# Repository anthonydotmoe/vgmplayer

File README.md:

# RP2040 → YM2151 VGM Player

"It's a work in progress"

### Backstory

**2018**
This project started out using an ATMEGA328P and Arduino, but I found that it
was hard to write fast enough code to play songs at full speed. I then found
the STM32 series of microcontrollers; It was promising, but I really didn't like
the SDK or the HAL that was provided for these parts. After a few years, the
Raspberry Pi Foundation released the Raspberry Pi Pico. I bought the board
during its pre-order stage simply because it's a $5 microcontroller. This new
board, with their own RP2040 chip, has one key feature that I didn't know at the
time will make this project viable for me. The Programmable I/O (PIO).

**2022**
I finally got to looking at the datasheet for this board during DEFCON 2022,
where they used the RP2040 for their interactive badge. The PIO section caught
my eye, but I didn't look into it until a month later.

When I read the examples they had for driving WS2812 LED strips, I realized
what I could do with this extra power. I could easily get data to the chip on
time, every time; and have plenty of time for drawing a UI to a screen,
fetching data from an SD card over SPI, and in the future, emulating other
sound chips for game systems with AD/PCM and other chips.

### Hardware

I made this development board for the project.

GPIO 0-7 are connected to D0-D7 on the YM2151. GPIO 8-10 are connected to the
`A0`, `WR`, and `CS` pins. I'm using SPI to connect to the SD card, and an
LTC6903 programmable clock generator making the main clock for the YM2151.

The supporting circuitry for the YM2151 was ripped from the same place I got
the chip from, a Yamaha CX5 Music Computer.

### Software

*To be documented... and written*

### Thank You

Special thanks to:

- [ReimuNotMoe](https://github.com/ReimuNotMoe) for their work on
  [TinyVGM](https://github.com/SudoMaker/TinyVGM). This framework for digesting
  the `.vgm` files is really helpful for me.
- [Aidan Lawrence](https://github.com/AidanHockey5) for open-sourcing his
  [YM2151 music player](https://github.com/AidanHockey5/YM2151_VGM_STM32) which
  got me started in the ATMEGA328P days.

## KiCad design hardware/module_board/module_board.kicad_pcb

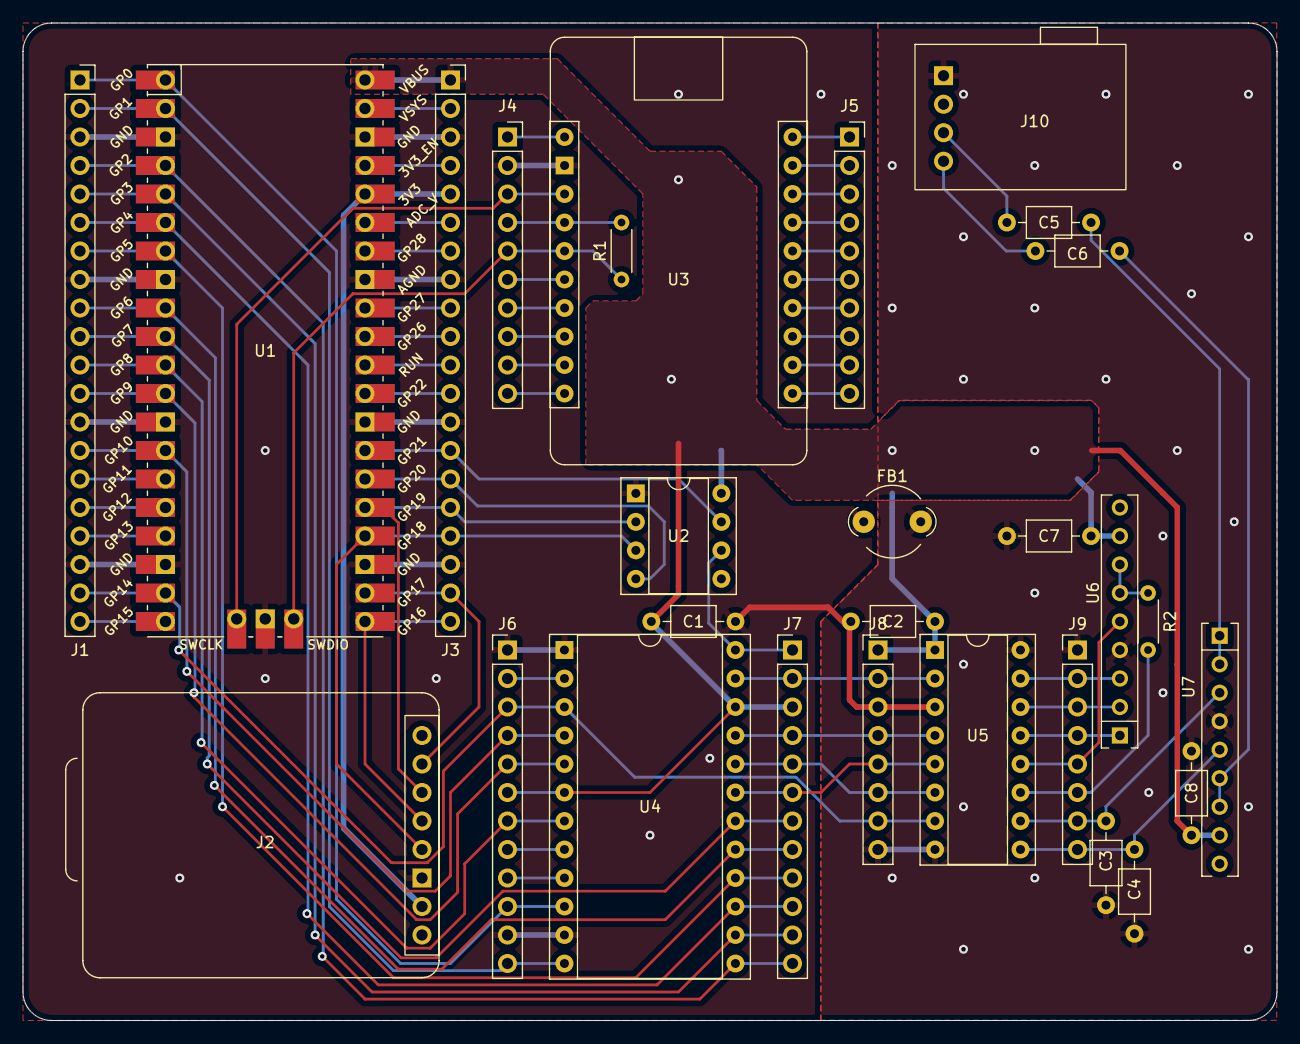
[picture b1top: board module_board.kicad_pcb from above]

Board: 2 copper layers, 111.8 x 88.9 mm, 28 parts (0 on the bottom side), 73 nets.

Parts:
C1, C2, C7, C8: 100nF; C_Axial_L3.8mm_D2.6mm_P7.50mm_Horizontal
C3, C4: 3300pF; C_Axial_L3.8mm_D2.6mm_P7.50mm_Horizontal
C5, C6: C; C_Axial_L3.8mm_D2.6mm_P7.50mm_Horizontal
FB1: 220Ω at 100MHz; LairdTech_28C0236-0JW-10
J1, J3: Conn_01x20_Female; PinSocket_1x20_P2.54mm_Vertical
J2: Micro_SD_Card_Breakout; Adafruit_Micro-SD_Card_Breakout
J4, J5: Conn_01x10_Female; PinSocket_1x10_P2.54mm_Vertical
J6, J7: Conn_01x12_Female; PinHeader_1x12_P2.54mm_Vertical
J8, J9: Conn_01x08_Female; PinHeader_1x08_P2.54mm_Vertical
J10: AudioJack4
R1: 1k; R_Axial_DIN0204_L3.6mm_D1.6mm_P5.08mm_Horizontal
R2: 100; R_Axial_DIN0204_L3.6mm_D1.6mm_P5.08mm_Horizontal
U1: Pico; RPi_Pico_SMD_TH
U2: LTC6903; DIP-8_W7.62mm_Socket
U3: FT232H_Breakout; Adafruit_FT232H_Breakout
U4: YM2151; DIP-24_W15.24mm_Socket
U5: YM3012; DIP-16_W7.62mm_Socket
U6, U7: NJM4556A; SIP-9_22.3x3mm_P2.54mm

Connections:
2151CLK: J7.1, U2.6 (CLK), U4.24 (ϕM)
+3V3: J2.7 (3V), J3.5, U1.36 (3V3)
/LTC OE: J3.14, U1.27 (GPIO21), U2.7 (OE)
/LTC ~CS: J3.15, U1.26 (GPIO20), U2.4 (~CS)
/SD ~CS: J2.2 (~CS), J3.19, U1.22 (GPIO17)
/SPI0 MISO: J2.4 (DO), J3.20, U1.21 (GPIO16)
/SPI0 MOSI: J2.3 (DI), J3.16, U1.25 (GPIO19), U2.2 (SDI)
/SPI0 SCK: J2.5 (CLK), J3.17, U1.24 (GPIO18), U2.3 (SCK)
/SWCLK: J4.3, U1.41 (SWCLK), U3.3 (D0)
/SWDIO: J4.5, R1.1, U1.43 (SWDIO), U3.5 (D2)
/YM_Output/3012CLK: J7.2, J8.2, U4.23 (ϕ1), U5.2 (CLKϕ1)
/YM_Output/BC: J9.3, U5.14 (BC), U6.2 (-)
/YM_Output/CH-1: C4.1, J9.8, U5.9 (OUT-CH1), U7.5 (+)
/YM_Output/CH-2: C3.1, J9.7, U5.10 (OUT-CH2), U7.3 (+)
/YM_Output/COM: J9.6, R2.1, U5.11 (COM)
/YM_Output/CT1: J6.8, U4.8 (CT1)
/YM_Output/CT2: J6.9, U4.9 (CT2)
/YM_Output/L-OUT_{AMP}: C6.1, U7.6 (-), U7.7
/YM_Output/MP: J9.4, U5.13 (MP), U6.1
/YM_Output/OUT-L: C6.2, J10.4 (T)
/YM_Output/OUT-R: C5.2, J10.3 (R1)
/YM_Output/R-OUT_{AMP}: C5.1, U7.1, U7.2 (-)
/YM_Output/R_{B}: J9.2, U5.15 (RB), U6.3 (+)
/YM_Output/SH1: J7.5, J8.6, U4.20 (SHI1), U5.6 (SAM1)
/YM_Output/SH2: J7.6, J8.5, U4.19 (SHI2), U5.5 (SAM2)
/YM_Output/SO: J7.4, J8.4, U4.21 (SO), U5.4 (DATA)
/YM_Output/ToBUFF: J9.5, U5.12 (ToBUFF), U6.5 (+)
/YM_Output/~IRQ: J6.2, U4.2 (~IRQ)
D0: J1.1, J6.10, U1.1 (GPIO0), U4.10 (D0)
D1: J1.2, J6.12, U1.2 (GPIO1), U4.12 (D1)
D2: J1.4, J7.12, U1.4 (GPIO2), U4.13 (D2)
D3: J1.5, J7.11, U1.5 (GPIO3), U4.14 (D3)
D4: J1.6, J7.10, U1.6 (GPIO4), U4.15 (D4)
D5: J1.7, J7.9, U1.7 (GPIO5), U4.16 (D5)
D6: J1.9, J7.8, U1.9 (GPIO6), U4.17 (D6)
D7: J1.10, J7.7, U1.10 (GPIO7), U4.18 (D7)
GNDA: C3.2, C4.2, C7.2, C8.2, FB1.2, J8.8, J9.1, J10.1 (S), U5.8 (AGND(VSS)), U5.16 (AGND(VSS)), U6.4 (V-), U7.4 (V-)
GNDD: C1.1, C2.2, FB1.1, J1.3, J1.8, J1.13, J1.18, J2.6 (GND), J3.3, J3.8, J3.13, J3.18, J4.2, J6.1, J6.11, J8.3, U1.3 (GND), U1.8 (GND), U1.13 (GND), U1.18 (GND), U1.23 (GND), U1.28 (GND), U1.33 (AGND), U1.38 (GND), U1.42 (GND), U2.1 (GND), U3.2 (GND), U4.1 (Vss(GND)), U4.11 (Vss(GND)), U5.3 (DGND(VSS))
unnamed: J1.15, U1.15 (GPIO11)
unnamed: J1.16, U1.16 (GPIO12)
unnamed: J1.17, U1.17 (GPIO13)
unnamed: J1.20, U1.20 (GPIO15)
unnamed: J3.2, U1.39 (VSYS)
unnamed: J3.4, U1.37 (3V3_EN)
unnamed: J3.6, U1.35 (ADC_VREF)
unnamed: J3.7, U1.34 (GPIO28_ADC2)
unnamed: J3.9, U1.32 (GPIO27_ADC1)
unnamed: J3.10, U1.31 (GPIO26_ADC0)
unnamed: J3.11, U1.30 (RUN)
unnamed: J3.12, U1.29 (GPIO22)
unnamed: J4.1, U3.1 (5V)
unnamed: J4.4, R1.2, U3.4 (D1)
unnamed: J4.6, U3.6 (D3)
unnamed: J4.7, U3.7 (D4)
unnamed: J4.8, U3.8 (D5)
unnamed: J4.9, U3.9 (D6)
unnamed: J4.10, U3.10 (D7)
unnamed: J5.1, U3.20 (C9)
unnamed: J5.2, U3.19 (C8)
unnamed: J5.3, U3.18 (C7)
unnamed: J5.4, U3.17 (C6)
unnamed: J5.5, U3.16 (C5)
unnamed: J5.6, U3.15 (C4)
unnamed: J5.7, U3.14 (C3)
unnamed: J5.8, U3.13 (C2)
unnamed: J5.9, U3.12 (C1)
unnamed: J5.10, U3.11 (C0)
unnamed: R2.2, U6.6 (-), U6.7
YM A0: J1.14, J6.4, U1.14 (GPIO10), U4.4 (A0)
YM ~CS: J1.11, J6.7, U1.11 (GPIO8), U4.7 (~CS)
YM ~RD: C1.2, C2.1, C7.1, C8.1, J3.1, J6.6, J7.3, J8.1, U1.40 (VBUS), U2.8 (V+), U4.6 (~RD), U4.22 (VDD(+5V)), U5.1 (VDD), U6.8 (V+), U7.8 (V+)
YM ~WR: J1.12, J6.5, U1.12 (GPIO9), U4.5 (~WR)
~ICL: J1.19, J6.3, J8.7, U1.19 (GPIO14), U4.3 (~IC), U5.7 (~ICL)

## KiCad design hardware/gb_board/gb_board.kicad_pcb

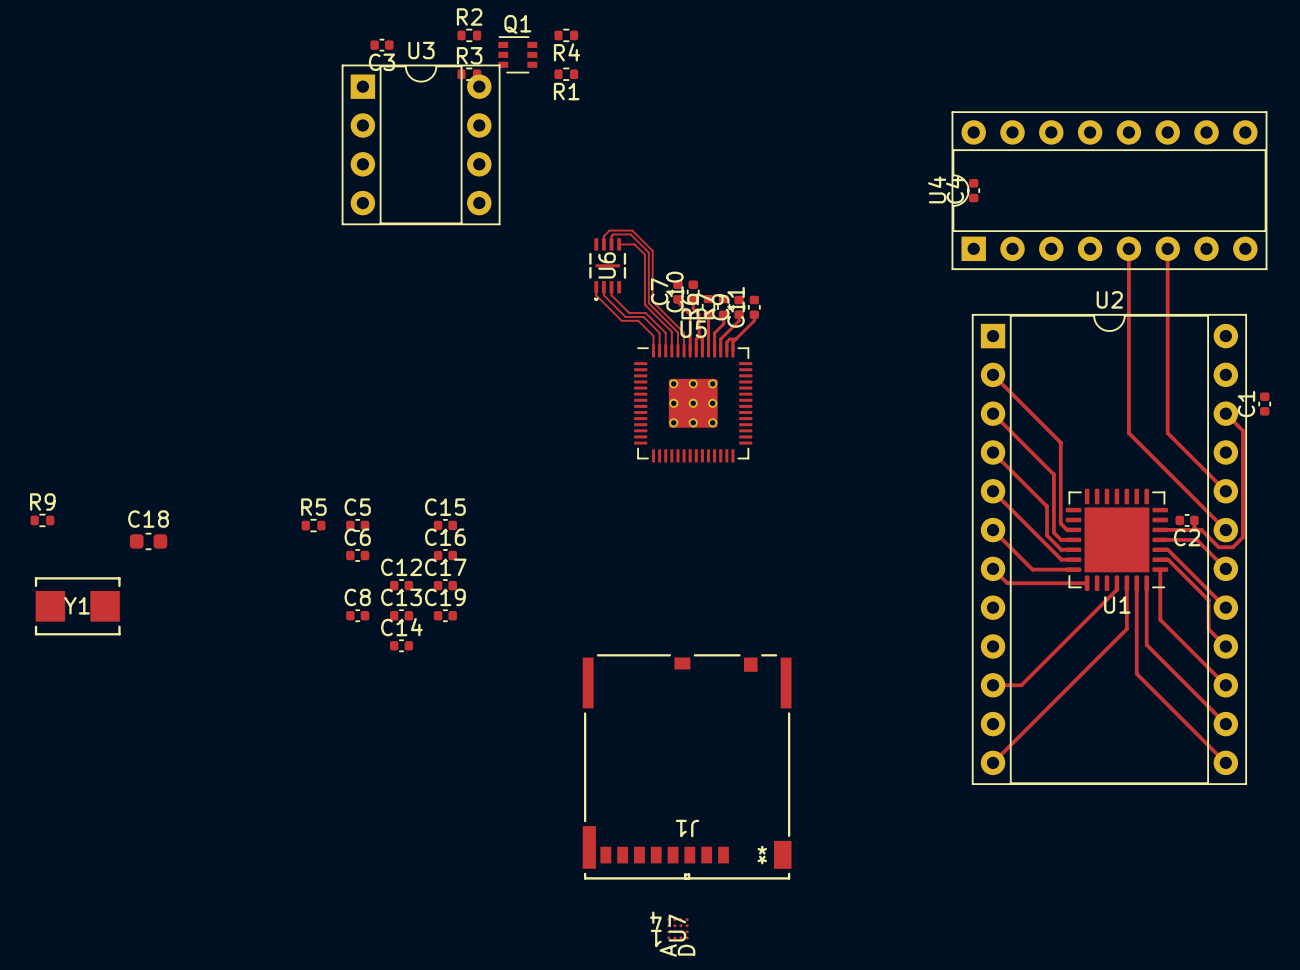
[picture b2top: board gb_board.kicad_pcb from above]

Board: 2 copper layers, 37 parts (0 on the bottom side), 40 nets.

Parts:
C1, C2, C3, C4: 0.1uF; C_0402_1005Metric
C5, C6: 27p; C_0402_1005Metric
C7, C8, C9, C10, C11, C12, C13, C14, C15, C16, C17, C19: 100n; C_0402_1005Metric
C18: 10u; C_0603_1608Metric
J1: Micro_SD_Card_Det1; 503398-1892_MOL
Q1: BSS138PS; SOT-363_SC-70-6
R1, R2, R3, R4: 10k; R_0402_1005Metric
R5: 1k; R_0402_1005Metric
R6, R7: 27.4; R_0402_1005Metric
R9: DNF; R_0402_1005Metric
U1: MCP23017_ML; QFN-28-1EP_6x6mm_P0.65mm_EP4.25x4.25mm
U2: YM2151; DIP-24_W15.24mm_Socket
U3: LTC6903; DIP-8_W7.62mm_Socket
U4: YM3012; DIP-16_W7.62mm_Socket
U5: RP2040; RP2040-QFN-56
U6: W25Q16JVUXIQ; W25Q16JVUXIQ_WIN
U7: EMIF06-MSD04F3; FLIPCHIP16_STM
Y1: ABM3-12.000MHZ-D2Y-T; XTAL_ABM3_ABR

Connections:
+1V1: C7.1, C8.1, C9.1, U5.23 (DVDD), U5.45 (VREG_VOUT), U5.50 (DVDD)
+3V3: C3.1, C10.1, C11.1, C12.1, C13.1, C14.1, C15.1, C16.1, C17.1, C18.1, C19.1, J1.4 (VDD), Q1.2 (G1), Q1.5 (G2), R1.1, R2.1, R9.1, U3.8 (V+), U5.1 (IOVDD), U5.10 (IOVDD), U5.22 (IOVDD), U5.33 (IOVDD), U5.42 (IOVDD), U5.43 (ADC_AVDD), U5.44 (VREG_IN), U5.48 (USB_VDD), U5.49 (IOVDD), U6.8 (VCC)
+5V: C1.1, C2.1, C4.1, R3.1, R4.1, U1.5 (VDD), U2.22 (VDD(+5V)), U4.1 (VDD)
/RP2040/QSPI_D0: U5.53 (QSPI_SD0), U6.5 (DI(IO0))
/RP2040/QSPI_D1: U5.55 (QSPI_SD1), U6.2 (DO(IO1))
/RP2040/QSPI_D2: U5.54 (QSPI_SD2), U6.3 (IO2)
/RP2040/QSPI_D3: U5.51 (QSPI_SD3), U6.7 (IO3)
/RP2040/QSPI_F_~CS: R9.2, U5.56 (QSPI_SS), U6.1 (~CS)
/RP2040/QSPI_SCK: U5.52 (QSPI_SCLK), U6.6 (CLK)
/RP2040/RPUSB_N: R7.1, U5.46 (USB_DM)
/RP2040/RPUSB_P: R6.1, U5.47 (USB_DP)
/RP2040/SD_DET: J1.10 (DET_A), U5.36 (GPIO24)
/SAM1: U2.20 (SHI1), U4.6 (SAM1)
/SAM2: U2.19 (SHI2), U4.5 (SAM2)
/YM_SD: U2.21 (SO), U4.4 (DATA)
GNDA: C4.2, U4.8 (AGND(VSS)), U4.16 (AGND(VSS))
GNDD: C1.2, C2.2, C3.2, C5.1, C6.1, C7.2, C8.2, C9.2, C10.2, C11.2, C12.2, C13.2, C14.2, C15.2, C16.2, C17.2, C18.2, C19.2, J1.6 (VSS), J1.9 (DET_B), J1.11 (SHIELD), U1.6 (VSS), U1.11 (A0), U1.12 (A1), U1.13 (A2), U1.29 (EP), U2.1 (Vss(GND)), U2.11 (Vss(GND)), U3.1 (GND), U4.3 (DGND(VSS)), U6.4 (GND)
unnamed: C6.2, R5.1, Y1.2
unnamed: C5.2, U5.20 (XIN), Y1.1
unnamed: R5.2, U5.21 (XOUT)
SCL: Q1.4 (S2), R1.2, U5.7 (GPIO5)
SCL_5V: Q1.3 (D2), R3.2, U1.8 (SCK)
SDA: Q1.1 (S1), R2.2, U5.6 (GPIO4)
SDA_5V: Q1.6 (D1), R4.2, U1.9 (SDA)
YM_A0: U1.19 (GPA2), U2.4 (A0)
YM_D0: U1.25 (GPB0), U2.10 (D0)
YM_D1: U1.26 (GPB1), U2.12 (D1)
YM_D2: U1.27 (GPB2), U2.13 (D2)
YM_D3: U1.28 (GPB3), U2.14 (D3)
YM_D4: U1.1 (GPB4), U2.15 (D4)
YM_D5: U1.2 (GPB5), U2.16 (D5)
YM_D6: U1.3 (GPB6), U2.17 (D6)
YM_D7: U1.4 (GPB7), U2.18 (D7)
YM_DCLK: U2.23 (ϕ1), U4.2 (CLKϕ1)
YM_MCLK: U2.24 (ϕM), U3.6 (CLK)
YM_~CS: U1.22 (GPA5), U2.7 (~CS)
YM_~IC: U1.18 (GPA1), U2.3 (~IC), U4.7 (~ICL)
YM_~IRQ: U1.17 (GPA0), U2.2 (~IRQ)
YM_~RD: U1.21 (GPA4), U2.6 (~RD)
YM_~WR: U1.20 (GPA3), U2.5 (~WR)

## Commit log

2022-09-25 Add link to YM2151_Arcade_Classic
2022-09-25 Add hw_config.c
2022-09-28 Reconfigure no-OS-FatFS-SD-SPI-RPi-Pico submodule
2022-09-28 reconfigure libraries
2022-09-28 oops
2022-09-28 restore proper submodule
2022-09-28 reconfigure submodule
2022-09-28 try again with submodules
2022-09-28 starting over
2022-09-28 we'll get there
2022-09-28 Remove copy of TinyVGM
2022-09-28 Replace copy of TinyVGM with real TinyVGM
2022-09-28 change old references to old vgm library
2022-09-28 add a gitignore
2022-09-28 first draft pio programs
2022-09-28 first draft LTC6903 driver
2022-09-28 Mark .pio as Assembly
2022-09-28 Mark .pio files as Assembly
2022-09-28 formatting
2022-09-28 Refactor LTC6903
2022-09-29 Tested working SD card with LTC6903
2022-09-29 notes to help me walk through the bit shifting
2022-09-29 refine ignore
2022-09-30 finish pio program
2022-09-30 Fix addr/data byte order
2022-10-01 IT WORKS!!
    Slowing down execution of the data program
2022-10-01 quick and dirty looping
2022-10-01 bump SPI to 25MHz
2022-10-01 change clock divider, remove wait from irq
2022-10-02 rushed multi-file support, messed with timing
2022-10-02 Add note from ValleyBell
2022-10-02 mess with timing
2022-10-02 make ICL delay a #define
2022-10-02 add debugging messages
2022-10-02 Add song duration parsing
2023-02-24 add sharpmem library
2023-03-15 update no-OS-FatFS
2023-07-11 timing
2023-07-11 project restructure
2023-08-05 Add KiCAD sources
2023-08-05 fix vscode workspace
2026-05-14 update TinyVGM
2026-05-14 get debugging working
2026-05-14 Decouple VGM parse from playback. Use Core 1 to drive VGM player.
2026-05-14 disable FatFS LED blink
2026-05-14 fix 44.1kHz timer
2026-05-15 add core1 reset to let debugging work
